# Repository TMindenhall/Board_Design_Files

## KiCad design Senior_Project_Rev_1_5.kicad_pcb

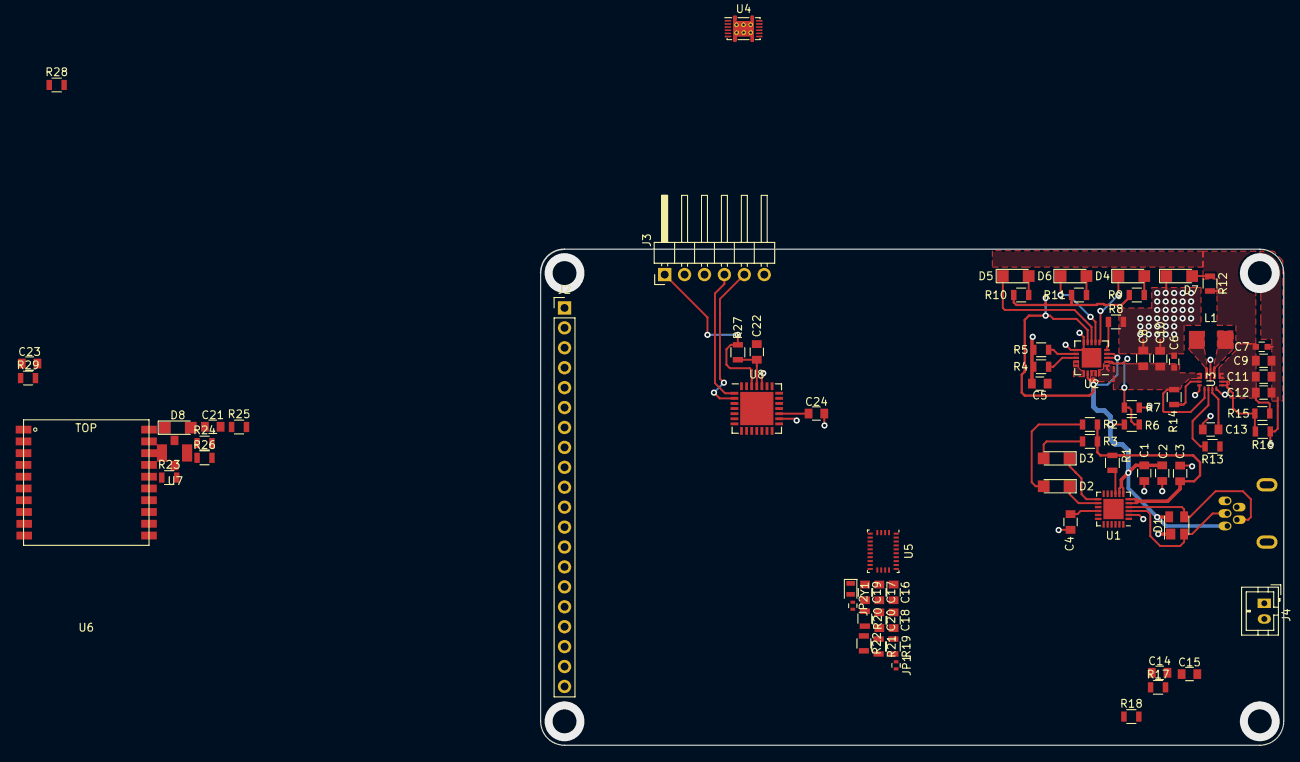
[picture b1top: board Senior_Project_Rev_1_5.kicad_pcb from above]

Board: 2 copper layers, 94.7 x 63.2 mm, 77 parts (1 on the bottom side), 65 nets.

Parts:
C1, C13, C14, C16, C17, C18, C21, C22, C23: .1uF; C_0805
C2, C3, C4, C5, C8, C10, C24: 10uF; C_0805
C6, C7: 10uF_6; C_0603
C9, C11, C12: 22uF; C_0805
C15: 1uF; C_0805
C19, C20: 22pF; C_0805
D1: SP0503BAHT; SOT-143
D2: TX_LED; LED_1206
D3: RX_LED; LED_1206
D4, D5, D6: LED; LED_1206
D7: 3V_LED; LED_1206
D8: FIX; LED_1206
J1: USB_B_Mini; USB_B_Mini_Molex
J2: TFT_INPUT; Pin_Header_Straight_1x20_Pitch2.54mm
J3: PicKit_INPUT; Pin_Header_Angled_1x06_Pitch2.54mm
J4: BATT_JST; JST_PH_B2B-PH-K_02x2.00mm_Straight
JP1, JP2: Jumper; R_0402
L1: 1.5uH; Inductor_BB
R1, R8, R14, R19, R20, R21, R22, R23, R27: 10k; R_0805
R2, R3, R9, R10, R11, R12, R18, R26: 1k; R_0805
R4: 2k; R_0805
R5, R7, R13: 100k; R_0805
R6: 270k; R_0805
R15: 470k; R_0805
R16: 150k; R_0805
R17: 10m; R_0805
R24, R25: 300; R_0805
R28, R29: 2.2k; R_0805
U1: CP2104; QFN-24-1EP_4x4mm_Pitch0.5mm
U2: MCP73871; QFN-20-1EP_4x4mm_Pitch0.5mm
U3: TPS63070
U4: BQ27441-G1; Texas_S-PDSO-N12
U5: BNO055; LGA-28_5.2x3.8mm_Pitch0.5mm
U6: MTK3339
U7: u_FL
U8: PIC32MX170F256B; QFN-28-1EP_6x6mm_Pitch0.65mm
Y1: 32kHz; Crystal_SMD_2012-2pin_2.0x1.2mm

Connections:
/BUCK/BOOST/EN: R14.2, U3.14
/BUCK/BOOST/FB: R15.2, R16.1, U3.5, U3.6
/BUCK/BOOST/PG: R13.2, U3.2
/CHARG CNTR/CHG_DN_AL: D6.1, U2.7
/CHARG CNTR/LBO_AL: D5.1, U2.8
/CHARG CNTR/PG_AL: D4.1, U2.6
/GPS/ANT: U6.11, U7.1
/GPS/FIX_AH: R26.2, U6.5
/IMU/PS0: JP1.2, U5.6
/IMU/PS1: JP2.1, U5.5
/PIC32/MCLR: J3.1, R27.2, U8.26
/PIC32/PGC1: J3.5, U8.2
/PIC32/PGD1: J3.4, U8.1
/PIC32/TFT_DC: J2.8, U8.18
/PIC32/TFT_RESET: J2.9, U8.20
/PIC32/TFT_SCK: J2.4, U8.22
/PIC32/TFT_SDI: J2.5, U8.19
/PIC32/TFT_SDO: J2.6, U8.21
/PIC32/TFT_SS: J2.7, U8.23
/PIC32/VCAP: C24.1, U8.17
/USB_SERIAL/RX_LED_AL: D3.1, U1.13
/USB_SERIAL/TX_LED_AL: D2.1, U1.14
/USB_SERIAL/USB_D+: D1.2, J1.3, U1.3
/USB_SERIAL/USB_D-: D1.3, J1.2, U1.4
DEB_RX: U1.21, U8.28
DEB_TX: U1.20, U8.7
GND: C1.2, C2.2, C3.2, C4.2, C5.2, C6.2, C7.2, C8.2, C9.2, C10.2, C11.2, C12.2, C13.2, C14.2, C15.2, C16.2, C17.2, C18.2, C19.1, C20.1, C21.2, C22.2, C23.2, C24.2, D1.1, D7.1, D8.1, J1.5, J1.6, J2.1, J3.3, J4.1, R4.2, R5.2, R7.2, R8.2, R16.2, U1.2, U1.25, U2.10, U2.11, U2.21, U3.4, U3.10, U3.15, U4.3, U4.13, U5.2, U5.10, U5.15, U5.16, U5.17, U5.18, U5.25, U6.3, U6.8, U6.12, U6.19, U7.2, U7.3, U7.4, U8.5, U8.16, U8.24
GPS_RX: R24.1, U8.9
GPS_TX: R25.1, U8.8
unnamed: C4.1, U1.16
unnamed: C13.1, U3.3
unnamed: C14.1, U4.5
unnamed: C18.1, U5.9
unnamed: C19.2, U5.26, Y1.1
unnamed: C20.2, U5.27, Y1.2
unnamed: D2.2, R2.2
unnamed: D3.2, R3.2
unnamed: D4.2, R9.2
unnamed: D5.2, R10.2
unnamed: D6.2, R11.2
unnamed: D7.2, R12.1
unnamed: D8.2, R26.1
unnamed: JP1.1, R21.2
unnamed: JP2.2, R22.2
unnamed: L1.1, U3.9
unnamed: L1.2, U3.11
unnamed: R1.2, U1.9
unnamed: R4.1, U2.13
unnamed: R5.1, U2.12
unnamed: R6.2, R7.1, U2.2
unnamed: R8.1, U2.5
unnamed: R18.2, U4.10
unnamed: R19.2, U5.4
unnamed: R20.2, U5.11
unnamed: R23.2, U6.2
unnamed: R24.2, U6.9
unnamed: R25.2, U6.10
PR_3V3_BB: C7.1, C9.1, C11.1, C12.1, C16.1, C17.1, C21.1, C22.1, C23.1, J2.2, J2.10, J3.2, R12.2, R13.1, R15.1, R19.1, R20.1, R21.1, R22.1, R23.1, R27.1, R28.1, R29.1, U3.7, U3.8, U5.3, U5.28, U6.1, U8.10, U8.25
PR_CP_3V3: C3.1, R1.1, R2.1, R3.1, U1.5, U1.6
SCL: R28.2, U4.2, U5.19, U8.14
SDA: R29.2, U4.1, U5.20, U8.15
V_BAT_IN: C15.1, J4.2, R17.1, R18.1, U4.6, U4.8
V_BAT_OUT: C5.1, R17.2, U2.14, U2.15, U2.16, U4.7
V_CHG_OUT: C6.1, C8.1, C10.1, R14.1, U2.1, U2.20, U3.1, U3.12, U3.13
V_USB_BUS: C1.1, C2.1, D1.4, J1.1, R6.1, R9.1, R10.1, R11.1, U1.7, U1.8, U2.3, U2.4, U2.9, U2.17, U2.18, U2.19

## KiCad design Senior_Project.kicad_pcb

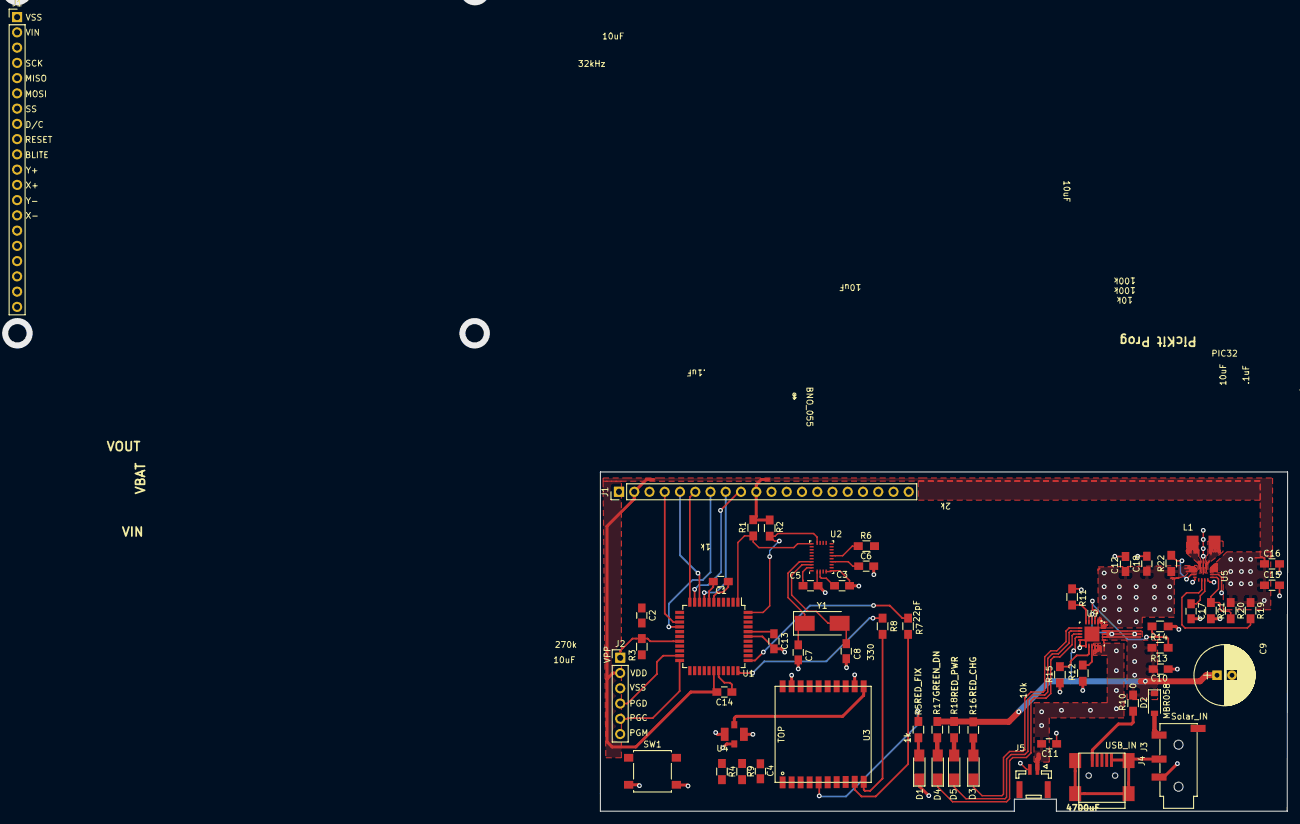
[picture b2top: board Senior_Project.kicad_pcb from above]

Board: 2 copper layers, 114.5 x 56.5 mm, 61 parts (1 on the bottom side), 62 nets.

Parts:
C1, C6, C10, C11, C12, C15, C18: 10uF; C_0805_HandSoldering
C2, C3, C4, C5, C13, C14, C17: .1uF; C_0805_HandSoldering
C7, C8: 22pF; C_0805_HandSoldering
C9: 4700uF; CP_Radial_D10.0mm_P2.50mm
C16: 47uF; C_0805_HandSoldering
D1: FIX_LED_RED; LED_1206_HandSoldering
D2: MBR0580; D_SOD-123
D3: RED_CHG; LED_1206_HandSoldering
D4: GREEN_DN; LED_1206_HandSoldering
D5: RED_PWR; LED_1206_HandSoldering
J1, J1#2: TFT OUTPUT; Pin_Header_Straight_1x20_Pitch2.54mm
J2: Conn_01x06_Male; Pin_Header_Straight_1x06_Pitch2.54mm
J3: Solar_IN; PJ320D_3.5mm_Jack
J4: USB_IN; USB_Mini-B
J5: BATT_JST; JST_GH_BM02B-GHS-TBT_02x1.25mm_Straight
J6: CR2032; Keystone_1058_1x2032-CoinCell
L1: 1.5uH; Inductor_BB
R1, R2: 2.2k; R_0805_HandSoldering
R3, R6, R9, R16, R17, R18: 1k; R_0805_HandSoldering
R4, R11, R22: 10k; R_0805_HandSoldering
R5: 1K; R_0805_HandSoldering
R7, R8: 330; R_0805_HandSoldering
R10: 0; R_0805_HandSoldering
R12: 2k; R_0805_HandSoldering
R13: 270k; R_0805_HandSoldering
R14, R15, R19: 100k; R_0805_HandSoldering
R20: 470k; R_0805_HandSoldering
R21: 150k; R_0805_HandSoldering
SW1: RESET; SW_SPST_B3S-1000
U1: PIC32MX170F256D-IPT; TQFP-44_10x10mm_Pitch0.8mm
U2: BNO055; LGA-28_5.2x3.8mm_Pitch0.5mm
U3: MTK3339
U4: u_FL
U5: TPS63070
U9: MCP73871-1AA; QFN20-Microchip
Y1: 32kHz; Crystal_SMD_0603-2pin_6.0x3.5mm_HandSoldering

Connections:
+3V3: C3.1, C4.2, C5.2, C13.1, C14.1, C15.1, C16.1, J1.2, J1.10, J1#2.2, J2.2, R1.1, R2.1, R4.1, R19.1, R20.1, U1.28, U1.40, U2.3, U2.28, U3.1, U5.7, U5.8
ANT: U3.11, U4.1
CS: J1.7, J1#2.7, U1.15
D\C: J1.8, J1#2.8, U1.8
FIX: R5.1, U3.5
IM0: J1.18, J1#2.18
IM1: J1.17, J1#2.17
IM2: J1.16, J1#2.16
IM3: J1.15, J1#2.15
MISO: J1.5, J1#2.5, U1.9
MOSI: J1.6, J1#2.6, U1.11
unnamed: C1.1, U1.7
unnamed: C2.1, U1.17
unnamed: C6.1, U2.9
unnamed: C7.2, U2.26, Y1.1
unnamed: C8.2, U2.27, Y1.2
unnamed: C17.1, U5.3
unnamed: D1.2, R5.2
unnamed: D2.2, J3.1
unnamed: D3.1, U9.6
unnamed: D3.2, R16.2
unnamed: D4.1, U9.8
unnamed: D4.2, R17.2
unnamed: D5.1, U9.7
unnamed: D5.2, R18.2
unnamed: J1.3, J1#2.3
unnamed: J3.2, J4.5, J4.6
unnamed: J4.1, R10.2
unnamed: L1.1, U5.9
unnamed: L1.2, U5.11
unnamed: R6.1, U2.11
unnamed: R7.1, U3.9
unnamed: R8.1, U3.10
unnamed: R9.1, U3.2
unnamed: R12.1, U9.13
unnamed: R13.2, R14.1, U9.2
unnamed: R15.1, U9.12
unnamed: R19.2, U5.2
unnamed: R20.2, R21.1, U5.5
unnamed: R22.2, U5.14
PGC: J2.5, U1.22
PGD: J2.4, U1.21
RESET: R3.2, R4.2, R6.2, R9.2, SW1.1
RX: R7.2, U1.34
SCL: R2.2, U1.44, U2.19
SDA: R1.2, U1.1, U2.20
SD_CS: J1.19, J1#2.19
SD_Detect: J1.20, J1#2.20
SPI_CLK: J1.4, J1#2.4, U1.14
TFT_RESET: J1.9, J1#2.9, U1.10
THERM: R11.1, U9.5
TX: R8.2, U1.33
VBAT: C11.1, J5.1, U9.14, U9.15, U9.16
VCOIN: J6.1, U3.4
VIN: C9.1, C10.1, D2.1, R10.1, R13.1, R16.1, R17.1, R18.1, U9.3, U9.4, U9.9, U9.17, U9.18, U9.19
VOUT: C12.1, C18.1, R22.1, U5.1, U5.12, U5.13, U9.1, U9.20
VSS: C1.2, C2.2, C3.2, C4.1, C5.1, C6.2, C7.1, C8.1, C9.2, C10.2, C11.2, C12.2, C13.2, C14.2, C15.2, C16.2, C17.2, C18.2, D1.1, J1.1, J1#2.1, J2.3, J3.3, J5.2, J6.2, R11.2, R12.2, R14.2, R15.2, R21.2, SW1.2, U1.6, U1.16, U1.29, U1.39, U2.2, U2.5, U2.6, U2.15, U2.16, U2.25, U3.3, U3.8, U3.12, U3.19, U4.2, U4.3, U4.4, U5.4, U5.6, U5.10, U5.15, U9.10, U9.11, U9.21
X+: J1.12, J1#2.12
X-: J1.14, J1#2.14
Y+: J1.11, J1#2.11
Y-: J1.13, J1#2.13
~MCLR\Vpp: J2.1, R3.1, U1.18

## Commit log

2019-04-08 Rev1.5
2019-04-25 Arch_Drawing
2019-04-25 Flowchart
